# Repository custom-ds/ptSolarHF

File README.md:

# ptSolarHF
The ptSolar is the newest version of Project: Traveler's series of APRS trackers. The ptSolar has been designed and optimized for low-power operation, especially when using a solar panel.

Under the hood, the ptSolar runs on the same __Microchip ATMega328p__ microcontroller that the other trackers have been using for years, although this board runs at a lower 3.3 volt level, and a slower 8MHz clock speed.

A 2m VHF transmitter is provided by the __SA818S-V__ transmitter-on-a-chip system, which means it's frequency agile and can be used throughout the world.

The GPS receiver is utilizes the __ATGM336H__ GPS engine which has a light-weight footprint while being a cost-effective solution. The ATGM336H is capable of position reports in excess of 60,000', making it a suitable solution for high altitude (latex) balloons traveling to over 100,000'.

## The Circuit Board
The circuit board is designed in Kicad and features a 4-layer design with castellated solder points for the attached solar panels.

The ptSolar is currently in the prototyping stages. Version 1.1.0 of the PCB was the initial design that was first built in early 2025, and includes the ATMega328p microcontroller, an ATGM336H GPS receiver, and the SA818S-V VHF transmitter. VHF signal filtering is provided by a 3-pole pi filter, reducing spurious harmonic output to well within Part 97 specifications.

## The Breakout Board
A Breakout board has been developed that can be temporarily or permanently paired to the top of the ptSolar tracker. The breakout includes a second ISCP programming port, a second serial data interface for configuring the tracker, a Sparkfun Qwiic connector for interfacing with other I2C sensors.

There is also a 2.1mm barrel jack for accepting power from a battery pack, along with the required 5V regulator when operating at higher supplied voltages. 

The Breakout Board mates to the tracker with a female .1" header connecting into the 6-pin (ISCP) and 8-pin (Serial, I2C) plugs on the ptSolar.

## Preparing the IDE for the Firmware
In the Arduino IDE and go to File &rarr; Preferences.  In the Additional Boards Manager URLs field, add the URL to the Project: Traveler website .json file:

```
https://www.projecttraveler.org/downloads/package_projecttraveler_index.json
```

Note that if there's already something in that field, you can click the small icon to the right of the text field where you are allowed to enter multiple entries on multiple lines.

Click OK to close the preferences dialog.  Then go to Tools &rarr; Boards &rarr; Boards Manager.

When the Boards Manager opens, select "Contributed" from the Type drop-down.  In the resulting list, you should find the Project Traveler Boards by Project Traveler option.  Click the Install button in the lower-right corner.

Close out of the Boards Manager dialog, and the back under Tools &rarr; Board, you should see "ptSolar Tracker (Arduino as ISP)" near the bottom of the list. 

## Setting the Controller Flags
If this is a brand new ptSolar board that has never been programmed before, there are several commands that must be run from a DOS command prompt. If the ptSolar was purchased as an assembled and tested kit, you can skip these steps.

The fuses are to be set as follows:
* Low: 0xFF
* High: 0xD6
* Extended: 0xFD

To program the fuses using the AVRDude tool (which is included in the Arduino IDE, and works with the Arduino As ISP programmer), open a command prompt on the PC.

```
C:\> cd \Program Files (x86)\Arduino\hardware\tools\avr\bin
C:\...> avrdude.exe -p m328p -b 19200 -c avrisp -C ..\etc\avrdude.conf -P comX* -U lfuse:w:0xDF:m -U hfuse:w:0xD6:m -U efuse:w:0xFD:m
```
Depending on your installation of the Arduino IDE, your avrdude may also be found in:

```
C:\Users\{Username}\AppData\Local\Arduino15\packages\arduino\tools\avrdude\6.3.0-arduino17\bin
```

This will write the fuses to the new processor.  To verify that the fuses have been written, run these commands:

```
avrdude.exe -p m328p -b 19200 -c avrisp -C ..\etc\avrdude.conf -P comX* -U lfuse:w:0xFF:m -U hfuse:w:0xD6:m -U efuse:w:0xFD:m 
```

\* Replace "comX" with whatever Com port your ArduinoISP is enumerating on.

### Verifying the Fuses
```
C:\...> avrdude.exe -p m328p -b 19200 -c avrisp -C ..\etc\avrdude.conf -P comX* -U lfuse:r:lowfuse:h -U hfuse:r:highfuse:h -U efuse:r:exfuse:h
C:\...> type lowfuse
C:\...> type highfuse
C:\...> type exfuse
```

\* Replace "comX" with whatever Com port your ArduinoISP is enumerating on.

## Loading the Firmware
To program the ptSolar, open the firmware Sketch in this GitHub Repository in the Arduino IDE. 

Go to the Tools &rarr; Board menu, select the "ptSolar Tracker (Arduino as ISP)" from the list of targets.  

The ptSolar boards are automatically configured to use the Arduino as ISP programmer to load the firmware onto the tracker boards, so no further configuration is necessary. Click the Upload button which will cause the Sketch to compile and will program to the ATmega328 processor similarly to how a normal Arduino board is programmed.

Sometimes it is necessary to apply external power to the ptSolar Tracker, depending on how much current the Programmer board is capable of sourcing.

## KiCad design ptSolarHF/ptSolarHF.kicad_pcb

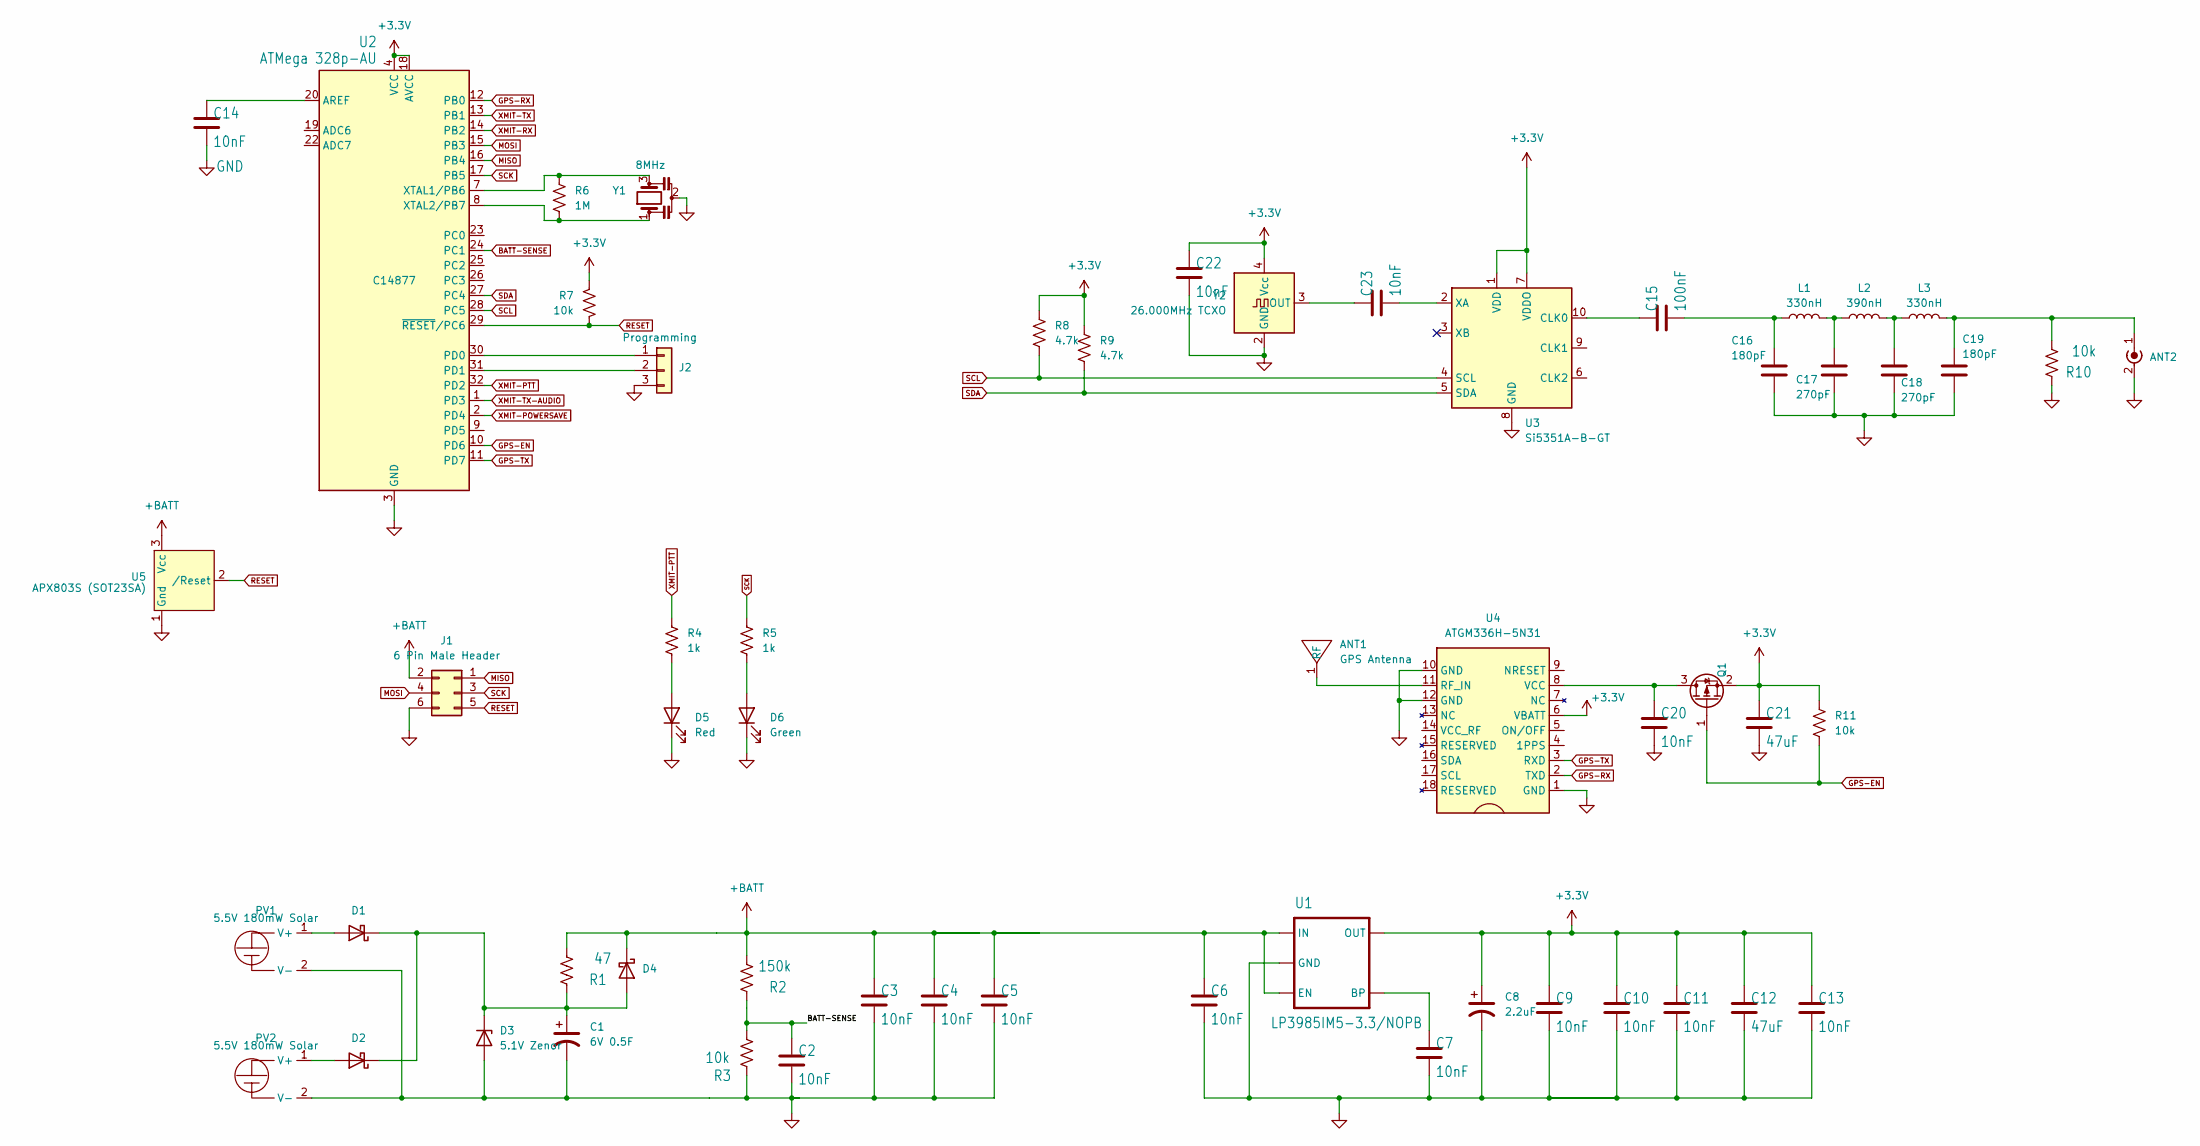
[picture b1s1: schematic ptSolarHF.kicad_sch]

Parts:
ANT1: GPS Antenna; Pulse ANT8010LL05R1575A Antenna; Digikey 553-ANT8010LL05R1575ACT-ND
ANT2: SMA Edge Mount (Optional); SMA_Samtec_SMA-J-P-H-ST-EM1_EdgeMount; Digikey CON-SMA-EDGE-S-ND
C1: 6V 0.5F; CDS CSP Super Cap 8mm dia; Digikey 4688-CSP-6R0L504R-TW-ND
C2, C3, C4, C5, C6, C7, C9, C10, C11, C13, C14, C20, C22, C23: 10nF; C_0805_2012Metric; Digikey 399-1158-1-ND
C8: 2.2uF; C_0805_2012Metric; Digikey 445-1420-1-ND
C12, C21: 47uF; C_0805_2012Metric; Digikey 399-C0805C476M9PACTUCT-ND
C15: 100nF; C_0805_2012Metric; Digikey 399-C0805C104K5RACTUCT-ND
C16, C19: 180pF; C_0805_2012Metric; Digikey 490-11541-1-ND
C17, C18: 270pF; C_0805_2012Metric; Digikey 490-9738-1-ND
D1, D2, D4: CDBA340L-G Schottky; D_SMA; Digikey 641-1258-1-ND
D3: 5.1V Zenor; D_SOD-123; Digikey MMSZ5231B-FDICT-ND
D5: Red; D_0805_2012Metric; Digikey LTST-C171KRKT
D6: Green; D_0805_2012Metric; Digikey LTST-C171GKT
J1: 6 Pin Male Header; PinHeader_2x03_P2.54mm_Vertical; Digikey 732-5394-ND
J2: Programming; PinHeader_1x03_P2.54mm_Vertical; Digikey 732-5316-ND
L1, L3: 330nH; L_0805_2012Metric; Digikey 490-5672-1-ND
L2: 390nH; L_0805_2012Metric; Digikey 490-5673-1-ND
PV1, PV2: 5.5V 180mW Solar; PowerFilm MPT3.6-75; Digikey 1996-1020-ND
Q1: DMP2004K-7; SOT-23; Digikey DMP2004KDICT-ND
R1: 47; R_2512_6332Metric; Digikey YAG3404CT-ND
R2: 150k; R_0805_2012Metric; Digikey 311-150KCRCT-ND
R3, R7, R10, R11: 10k; R_0805_2012Metric; Digikey 13-RT0805FRD0710KLCT-ND
R4, R5: 1k; R_0805_2012Metric; Digikey 311-1.0KARCT-ND
R6: 1M; R_0805_2012Metric; Digikey 311-1.0MARCT-ND
R8, R9: 4.7k; R_0805_2012Metric; Digikey 311-4.7KARCT-ND
U1: LP3985IM5-3.3/NOPB; SOT-23-5; Digikey LP3985IM5-3.3/NOPBCT-ND
U2: ATMega 328p-AU; TQFP-32_7x7mm_P0.8mm; Digikey ATMEGA328P-AU-ND
U3: Si5351A-B-GT; MSOP-10_3x3mm_P0.5mm; Digikey 336-2399-5-ND
U4: ATGM336H-5N31; Digikey ALIEXPRESS
U5: APX803S (SOT23SA); SOT-23; Digikey APX803S-31SA-7DICT-ND
Y1: 8MHz; Resonator_SMD_Murata_CSTxExxV-3Pin_3.0x1.1mm; Digikey 490-CSTNE8M00G520000R0CT-ND
Y2: 26.000MHz TCXO; Oscillator_SMD_SeikoEpson_TG2520SMN-xxx-xxxxxx-4Pin_2.5x2.0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; LCSC C3013793

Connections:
+3.3V: C8.1, C9.1, C10.1, C11.1, C12.1, C13.1, C21.1, C22.1, Q1.2 (S), R7.1, R8.1, R9.1, R11.1, U1.5 (OUT), U2.4 (VCC), U2.6 (VCC), U2.18 (AVCC), U3.1 (VDD), U3.7 (VDDO), U4.6 (VBATT), Y2.4 (Vcc)
+BATT: C3.1, C4.1, C5.1, C6.1, D4.1 (K), J1.2, R1.2, R2.2, U1.1 (IN), U1.3 (EN), U5.3 (Vcc)
BATT-SENSE: C2.1, R2.1, R3.2, U2.24 (PC1)
GND: ANT2.2 (Ext), C1.2, C2.2, C3.2, C4.2, C5.2, C6.2, C7.2, C8.2, C9.2, C10.2, C11.2, C12.2, C13.2, C14.2, C16.1, C17.1, C18.1, C19.1, C20.2, C21.2, C22.2, D3.2 (A), D5.1 (K), D6.1 (K), J1.6, J2.3, PV1.2 (V-), PV2.2 (V-), R3.1, R10.1, U1.2 (GND), U2.3 (GND), U2.5 (GND), U2.21 (GND), U3.8 (GND), U4.1 (GND), U4.10 (GND), U4.12 (GND), U5.1 (Gnd), Y1.2, Y2.2 (GND)
GPS-EN: Q1.1 (G), R11.2, U2.10 (PD6)
GPS-RX: U2.12 (PB0), U4.2 (TXD)
GPS-TX: U2.11 (PD7), U4.3 (RXD)
MISO: J1.1, U2.16 (PB4)
MOSI: J1.4, U2.15 (PB3)
unnamed: ANT1.1 (RF), U4.11 (RF_IN)
unnamed: ANT2.1 (In), C19.2, L3.2, R10.2
unnamed: C15.2, C16.2, L1.1
unnamed: C17.2, L1.2, L2.1
unnamed: C18.2, L2.2, L3.1
unnamed: D1.2 (A), PV1.1 (V+)
unnamed: C1.1, D1.1 (K), D2.1 (K), D3.1 (K), D4.2 (A), R1.1
unnamed: D2.2 (A), PV2.1 (V+)
unnamed: D5.2 (A), R4.2
unnamed: D6.2 (A), R5.2
unnamed: J2.1, U2.30 (PD0)
unnamed: J2.2, U2.31 (PD1)
unnamed: C20.1, Q1.3 (D), U4.8 (VCC)
unnamed: C7.1, U1.4 (BP)
unnamed: C14.1, U2.20 (AREF)
unnamed: R6.1, U2.7 (XTAL1/PB6), Y1.3
unnamed: R6.2, U2.8 (XTAL2/PB7), Y1.1
unnamed: C15.1, U3.10 (CLK0)
unnamed: C23.2, U3.2 (XA)
unnamed: C23.1, Y2.3 (OUT)
RESET: J1.5, R7.2, U2.29 (~RESET/PC6), U5.2 (/Reset)
SCK: J1.3, R5.1, U2.17 (PB5)
SCL: R8.2, U2.28 (PC5), U3.4 (SCL)
SDA: R9.2, U2.27 (PC4), U3.5 (SDA)
XMIT-POWERSAVE: U2.2 (PD4)
XMIT-PTT: R4.1, U2.32 (PD2)
XMIT-RX: U2.14 (PB2)
XMIT-TX: U2.13 (PB1)
XMIT-TX-AUDIO: U2.1 (PD3)

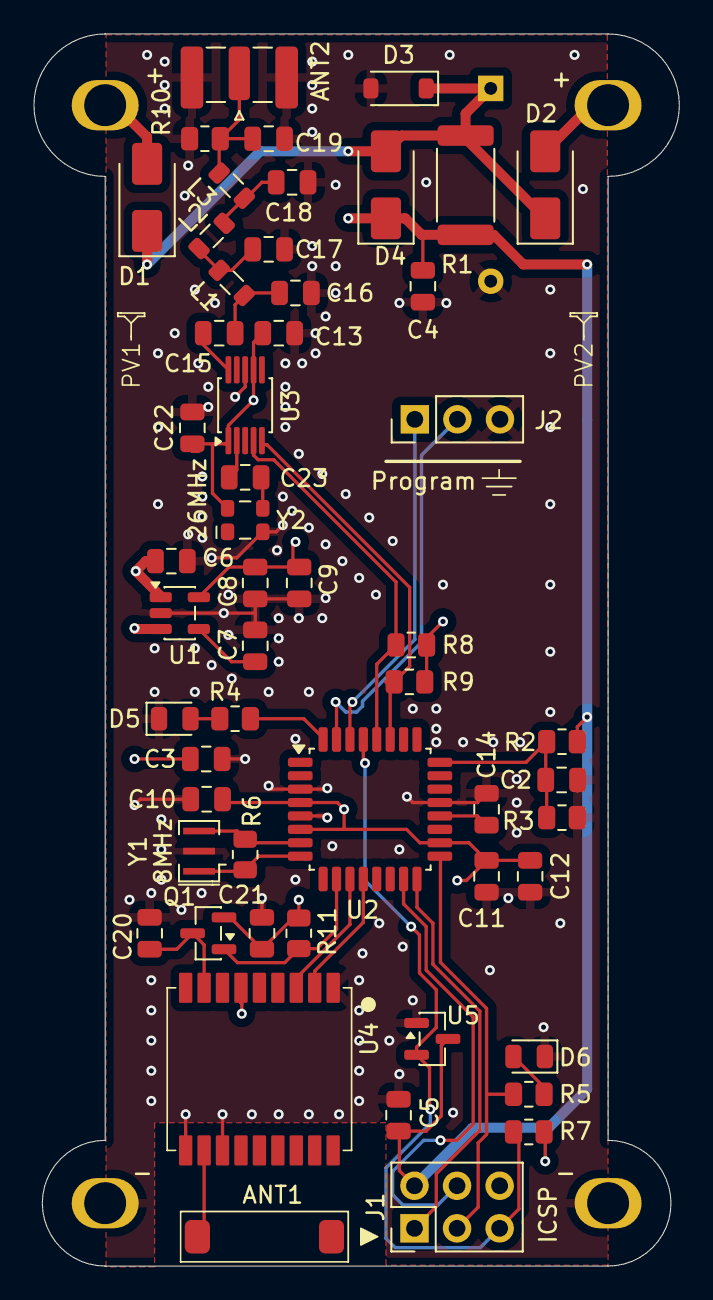
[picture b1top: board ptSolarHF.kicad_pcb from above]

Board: 4 copper layers, 38.5 x 73.5 mm, 57 parts (1 on the bottom side), 34 nets.

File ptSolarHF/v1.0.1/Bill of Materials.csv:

"Reference","Value","Datasheet","Footprint","Qty","DNP","Digikey","LCSC"
"ANT1","GPS Antenna","","Custom DS:Pulse ANT8010LL05R1575A Antenna","1","","553-ANT8010LL05R1575ACT-ND","C3284202"
"ANT2","SMA Edge Mount (Optional)","~","Connector_Coaxial:SMA_Samtec_SMA-J-P-H-ST-EM1_EdgeMount","1","","CON-SMA-EDGE-S-ND",""
"C1","6V 0.5F","~","Custom DS:CDS CSP Super Cap 8mm dia","1","","4688-CSP-6R0L504R-TW-ND",""
"C2,C3,C4,C5,C6,C7,C9,C10,C11,C13,C14,C20","10nF","~","Capacitor_SMD:C_0805_2012Metric","12","","399-1158-1-ND","C83170"
"C8","2.2uF","~","Capacitor_SMD:C_0805_2012Metric","1","","445-1420-1-ND","C107128"
"C12,C21","47uF","~","Capacitor_SMD:C_0805_2012Metric","2","","399-C0805C476M9PACTUCT-ND","C16780"
"C15","100nF","~","Capacitor_SMD:C_0805_2012Metric","1","","399-C0805C104K5RACTUCT-ND","C49678"
"C16,C19","180pF","~","Capacitor_SMD:C_0805_2012Metric","2","","490-11541-1-ND","C113826"
"C17,C18","270pF","~","Capacitor_SMD:C_0805_2012Metric","2","","490-9738-1-ND","C527183"
"D1,D2,D4","CDBA340L-G Schottky","~","Diode_SMD:D_SMA","3","","641-1258-1-ND","C22364900"
"D3","5.1V Zenor","~","Diode_SMD:D_SOD-123","1","","MMSZ5231B-FDICT-ND","C85181"
"D5","Red","~","Diode_SMD:D_0805_2012Metric","1","","LTST-C171KRKT","C2295"
"D6","Green","~","Diode_SMD:D_0805_2012Metric","1","","LTST-C171GKT","C2297 "
"J1","6 Pin Male Header","~","Connector_PinHeader_2.54mm:PinHeader_2x03_P2.54mm_Vertical","1","","732-5394-ND",""
"J2","Programming","~","Connector_PinHeader_2.54mm:PinHeader_1x03_P2.54mm_Vertical","1","","732-5316-ND",""
"L1,L3","330nH","~","Inductor_SMD:L_0805_2012Metric","2","","490-5672-1-ND","C184530"
"L2","390nH","~","Inductor_SMD:L_0805_2012Metric","1","","490-5673-1-ND","C108076"
"PV1,PV2","5.5V 180mW Solar","https://www.powerfilmsolar.com/hubfs/documents/spec%20sheets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","Custom DS:PowerFilm MPT3.6-75","2","","1996-1020-ND",""
"Q5","DMP2004K-7","","Package_TO_SOT_SMD:SOT-23","1","","DMP2004KDICT-ND","C332297"
"R1","47","~","Resistor_SMD:R_2512_6332Metric","1","","YAG3404CT-ND","C513678"
"R2","150k","~","Resistor_SMD:R_0805_2012Metric","1","","311-150KCRCT-ND","C114558"
"R3,R7,R10,R11","10k","~","Resistor_SMD:R_0805_2012Metric","4","","13-RT0805FRD0710KLCT-ND","C100047"
"R4,R5","1k","~","Resistor_SMD:R_0805_2012Metric","2","","311-1.0KARCT-ND","C95781"
"R6","1M","~","Resistor_SMD:R_0805_2012Metric","1","","311-1.0MARCT-ND","C107700"
"R8,R9","4.7k","~","Resistor_SMD:R_0805_2012Metric","2","","311-4.7KARCT-ND","C60816"
"U1","LP3985IM5-3.3/NOPB","https://www.ti.com/lit/ds/symlink/lp3985.pdf?HQS=dis-dk-null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","Package_TO_SOT_SMD:SOT-23-5","1","","LP3985IM5-3.3/NOPBCT-ND","C108877"
"U2","ATMega 328p-AU","https://ww1.microchip.com/downloads/en/DeviceDoc/Atmel-7810-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","Package_QFP:TQFP-32_7x7mm_P0.8mm","1","","ATMEGA328P-AU-ND","C14877"
"U3","Si5351A-B-GT","https://www.silabs.com/documents/public/data-sheets/Si5351-B.pdf","Package_SO:MSOP-10_3x3mm_P0.5mm","1","","336-2399-5-ND","C504891"
"U4","ATGM336H-5N31","https://www.tinytronics.nl/product_files/002176_ATGM336H.pdf","Custom DS:ATGM336H-5N31","1","","ALIEXPRESS","C90770"
"U5","APX803S (SOT23SA)","","Package_TO_SOT_SMD:SOT-23","1","","APX803S-31SA-7DICT-ND","C129757"
"Y1","8MHz","~","Crystal:Resonator_SMD_Murata_CSTxExxV-3Pin_3.0x1.1mm","1","","490-CSTNE8M00G520000R0CT-ND","C907975"
"Y2","27MHz Xtal - 7M-27.000MEEQ-T","~","Crystal:Crystal_SMD_3225-4Pin_3.2x2.5mm","1","","887-1328-1-ND","C2450429"

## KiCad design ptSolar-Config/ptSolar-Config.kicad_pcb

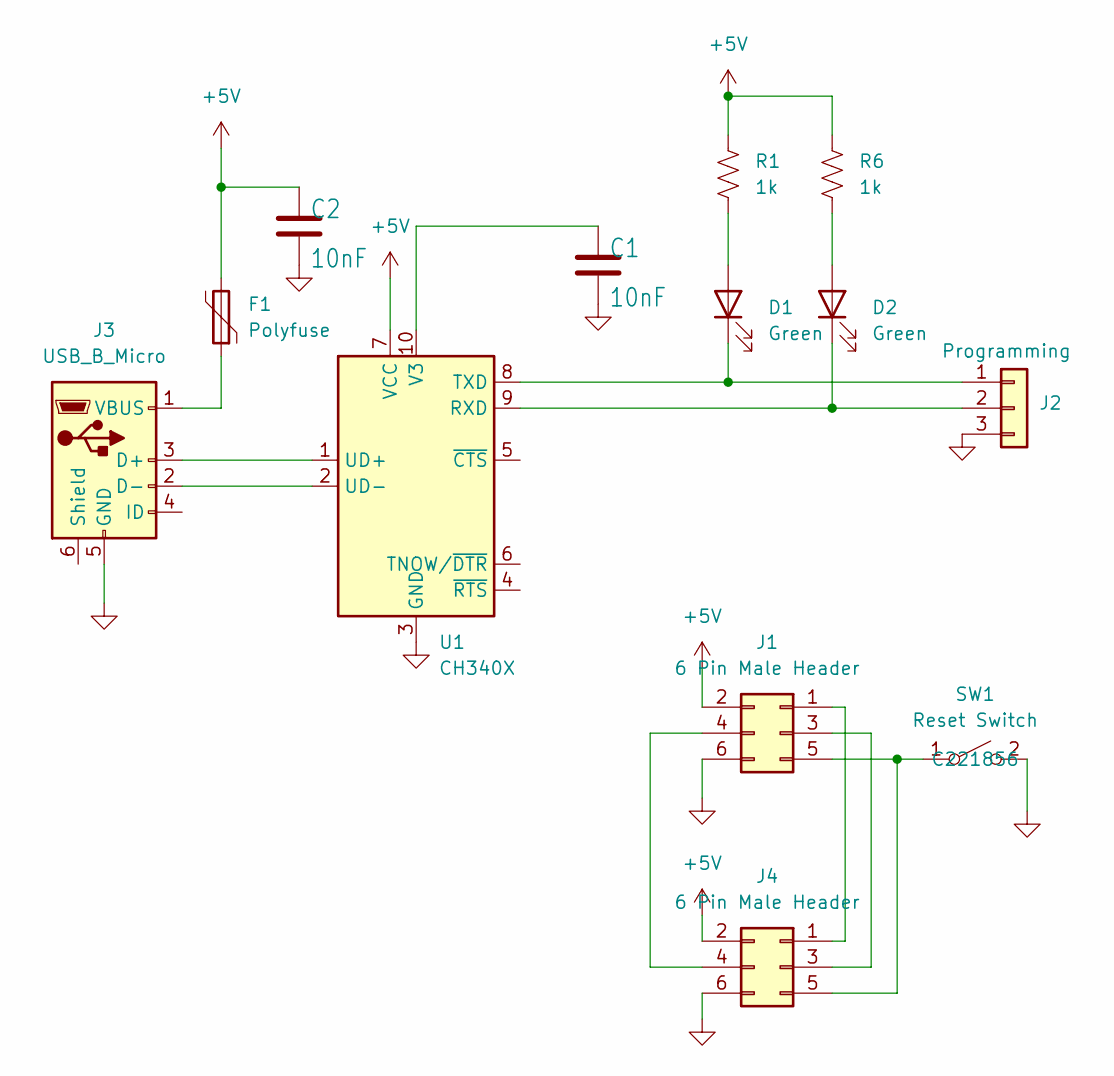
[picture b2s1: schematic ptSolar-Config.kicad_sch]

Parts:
C1, C2: 10nF; C_0805_2012Metric; Digikey 399-1158-1-ND
D1, D2: Green; D_0805_2012Metric; Digikey LTST-C171GKT
F1: Polyfuse; Fuse_1206_3216Metric; Digikey 507-1794-1-ND
J1, J4: 6 Pin Male Header; PinHeader_2x03_P2.54mm_Vertical; Digikey 732-5394-ND
J2: Programming; PinHeader_1x03_P2.54mm_Vertical; Digikey 732-5316-ND
J3: USB_B_Micro; USB_Micro-B_Wuerth_629105150521; LCSC C2894326
R1, R6: 1k; R_0805_2012Metric; Digikey 311-1.0KARCT-ND
SW1: Reset Switch; SW_SPST_PTS647_Sx38; Digikey CKN9104CT-ND
U1: CH340X; MSOP-10_3x3mm_P0.5mm; LCSC CH340X

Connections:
+5V: C2.1, F1.2, J1.2, J4.2, R1.1, R6.1, U1.7 (VCC)
GND: C1.2, C2.2, J1.6, J2.3, J3.5 (GND), J4.6, SW1.2 (B), U1.3 (GND)
unnamed: D1.2 (A), R1.2
unnamed: D1.1 (K), J2.1, U1.8 (TXD)
unnamed: D2.2 (A), R6.2
unnamed: D2.1 (K), J2.2, U1.9 (RXD)
unnamed: J1.1, J4.1
unnamed: J1.3, J4.3
unnamed: J1.4, J4.4
unnamed: J1.5, J4.5, SW1.1 (A)
unnamed: J3.3 (D+), U1.1 (UD+)
unnamed: J3.2 (D-), U1.2 (UD-)
unnamed: F1.1, J3.1 (VBUS)
unnamed: C1.1, U1.10 (V3)

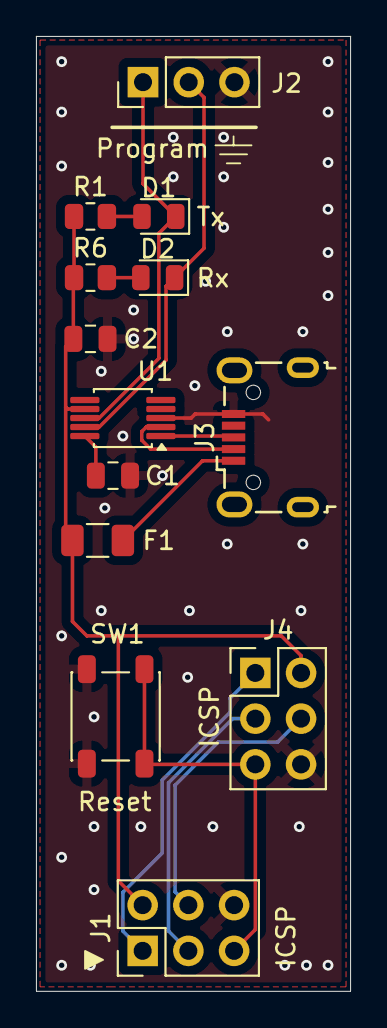
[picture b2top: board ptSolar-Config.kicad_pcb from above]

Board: 2 copper layers, 17.4 x 53.0 mm, 13 parts (0 on the bottom side), 14 nets.

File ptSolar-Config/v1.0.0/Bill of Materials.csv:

"Reference","Value","Datasheet","Footprint","Qty","DNP","Digikey","LCSC","LSCC"
"C1,C2","10nF","~","Capacitor_SMD:C_0805_2012Metric","2","","399-1158-1-ND","C83170",""
"D1,D2","Green","~","Diode_SMD:D_0805_2012Metric","2","","LTST-C171GKT","C2297 ",""
"F1","Polyfuse","~","Fuse:Fuse_1206_3216Metric","1","","507-1794-1-ND","C194142",""
"J1","6 Pin Male Header","~","Connector_PinHeader_2.54mm:PinHeader_2x03_P2.54mm_Vertical","1","","732-5394-ND","",""
"J2","Programming","~","Connector_PinHeader_2.54mm:PinHeader_1x03_P2.54mm_Vertical","1","","732-5316-ND","",""
"J3","USB_B_Micro","~","Connector_USB:USB_Micro-B_Wuerth_629105150521","1","","","C2894326",""
"R1,R6","1k","~","Resistor_SMD:R_0805_2012Metric","2","","311-1.0KARCT-ND","C95781",""
"SW1","Reset Switch","~","Button_Switch_SMD:SW_SPST_PTS647_Sx38","1","","CKN9104CT-ND","C221856",""
"U1","CH340X","https://cdn.sparkfun.com/assets/5/0/a/8/5/CH340DS1.PDF","Package_SO:MSOP-10_3x3mm_P0.5mm","1","","","CH340X",""

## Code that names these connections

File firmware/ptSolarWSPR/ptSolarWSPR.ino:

/*  WSPR_Si5351_wspr_enc_demo.ino
    Minimal WSPR beacon for ATmega328 (Uno/Nano) + Si5351 using:
      - Etherkit Si5351 library to generate the RF tones
      - wspr_enc.c (with nhash.c) to encode a WSPR message into 162 channel symbols

    References:
      - Etherkit Si5351 example shows centi-Hz use and WSPR spacing = 146 cHz. [ref]
      - WSPR protocol timing: 162 symbols, 1.4648 Hz spacing, 8192/12000 s per symbol. [ref]
*/


#define FIRMWARE_VERSION "1.6.0"
#define CONFIG_PROMPT "\n\n# "
#include "BoardDef.h"   //defines if this is a ptFlex, ptSolar, or ptSolarHF PCB board


#include <avr/wdt.h>

#include <si5351.h>
#include "wspr_enc.h"
#include "nhash.h"

#include <int.h>
#include <string.h>

#include "GPS.h"


#include "Wire.h"





// -------- USER CONFIG --------
static char    CALL[] = "W0ZC";
static char    GRID[] = "EM18";
static uint8_t PWR_dBm = 23;

//static const uint32_t WSPR_BASE_FREQ_HZ = 14097200UL;   // 14.095.600 + 1600Hz
static const uint32_t WSPR_BASE_FREQ_HZ = 21096200UL;   // 21.094.600 + 1600Hz
//static const uint32_t WSPR_BASE_FREQ_HZ = 28126200UL;   // 28.124.600 + 1600Hz
static const int32_t  SI5351_CORRECTION_PPB = 0;        // e.g. -1200 = -1.2 ppm
static const si5351_drive SI5351_CLK0_DRIVE = SI5351_DRIVE_8MA;
// ------ END USER CONFIG ------

static const uint16_t WSPR_TONE_SPACING_CENTI_HZ = 146; // ≈1.46 Hz
static const uint16_t WSPR_SYMBOL_COUNT           = 162;
static const uint16_t WSPR_TONE_MS                = 683; // 8192/12000 s


//PD0 is Serial Port RX
//PD1 is Serial Port TX
#define PIN_PTT_OUT 2     //PD2
//PD3 is not used
//PD4 is not used
#define PIN_AUDIO 5       //PD5   - Audio Annunciation
#define PIN_GPS_EN 6      //PD6
#define PIN_GPS_TX 7      //PD7

#define PIN_GPS_RX 8      //PB0
//PB1 is not used
//PB2 is not used
//PB3 is MOSI
//PB4 is MISO
#define PIN_LED 13        //PB5

//Analog Pins
//PC0 is not used
#define PIN_ANALOG_BATTERY A1   //PC1
//PC2 is not used
//PC3 is not used
//PC4 is SDA
//PC5 is SCL
//PC6 is reset and not available

Si5351 si5351;
static uint8_t wspr_symbols[WSPR_SYMBOL_COUNT];
GPS GPSParser(PIN_GPS_RX, PIN_GPS_TX, PIN_GPS_EN);                                      //Object that parses the GPS strings


static void build_wspr_symbols() {
    char pwr_str[4];
    itoa(PWR_dBm, pwr_str, 10);
    uint8_t mtype = wspr_enc(CALL, GRID, pwr_str, wspr_symbols); // fills 162 symbols

    // quick blink = message type
    for (uint8_t i = 0; i < mtype; i++)
    {
        wdt_reset();
        digitalWrite(PIN_PTT_OUT, HIGH);
        delay(80);
        digitalWrite(PIN_PTT_OUT, LOW);
        delay(80);
    }
}

static void transmit_wspr_once() {
    const uint64_t base_cHz = (uint64_t)WSPR_BASE_FREQ_HZ * 100ULL;

    // Serial.println("Starting WSPR transmission...");
    delay(100);
    si5351.output_enable(SI5351_CLK0, 1);
    digitalWrite(PIN_PTT_OUT, HIGH);

    for (uint16_t i = 0; i < WSPR_SYMBOL_COUNT; i++)
    {
        wdt_reset();
        // Serial.print("Transmitting symbol ");;
        // Serial.println(i);
        
        const uint8_t sym = wspr_symbols[i] & 0x03;
        const uint64_t f_cHz = base_cHz + (uint64_t)sym * (uint64_t)WSPR_TONE_SPACING_CENTI_HZ;
        si5351.set_freq(f_cHz, SI5351_CLK0);
        delay(WSPR_TONE_MS);
    }

    si5351.output_enable(SI5351_CLK0, 0);
    digitalWrite(PIN_PTT_OUT, LOW);
    Serial.println("WSPR transmission complete.");
    //delay(100);
}

void setup() {
    wdt_disable(); // disable the watchdog timer by default
    wdt_enable(WDTO_8S);    //Enable the Watchdog if configured
    wdt_reset();

    Serial.begin(19200);
    Serial.println("WSPR Si5351 Transmitter Demo");

    pinMode(PIN_PTT_OUT, OUTPUT);
    digitalWrite(PIN_PTT_OUT, HIGH);
    delay(1000);
    wdt_reset();

    // Starting the wire
    Serial.println("Wire begin");
    delay(100);
    Wire.begin();


    Serial.println("set bus speed");
    delay(100);
    Wire.setClock(100000); // Set to 400kHz

    byte error, address;
    int nDevices = 0;
/*
    Serial.println("Scanning I2C bus...");
    delay(100);
    for (address = 1; address < 127; address++)
    {
        wdt_reset();
        Serial.print("Checking address 0x");
        Serial.println(address, HEX);
        delay(100);
        Wire.beginTransmission(address);
        error = Wire.endTransmission();

        if (error == 0)
        {
            Serial.print(F("I2C device found at address 0x"));
            delay(100);
            if (address < 16)
                Serial.print('0');
            Serial.print(address, HEX);
            Serial.println(F("  !"));
            delay(100);
            nDevices++;
        }
        else if (error == 4)
        {
            Serial.print(F("Unknown error at address 0x"));
            delay(100);
            if (address < 16)
                Serial.print('0');
            Serial.println(address, HEX);
            delay(100);
        }
    }

    if (nDevices == 0)
        Serial.println(F("No I2C devices found\n"));
    else
        Serial.println(F("done\n"));

    delay(1000);
*/
    Serial.println(F("Initializing Si5351..."));
    delay(100);
    wdt_reset();
    si5351.init(SI5351_CRYSTAL_LOAD_10PF, 27000000, 0);

    Serial.println("Correction");
    delay(100);
    wdt_reset();
    si5351.set_correction(SI5351_CORRECTION_PPB, SI5351_PLL_INPUT_XO);

    Serial.println("Drive");
    delay(100);
    si5351.drive_strength(SI5351_CLK0, SI5351_CLK0_DRIVE);

    Serial.println("Output");
    delay(100);
    si5351.output_enable(SI5351_CLK0, 0);

    Serial.println("Done");
    delay(1000);

    Serial.println(F("Building WSPR symbols..."));
    delay(1000);
    build_wspr_symbols();
    Serial.println(F("Got them"));
    delay(1000);
    // Optional: wait for even minute before calling transmit_wspr_once()
    Serial.println("Press p to transmit WSPR once");

    GPSParser.setDebugNEMA(true); /// TODO: Need to pull this from Configuration
    GPSParser.setDebugLevel(2);   // Get full verbose output from the GPS
}

void loop() {
    byte byTemp;
    wdt_reset();
    
    if (Serial.available())
    {
        byTemp = Serial.read();
        if (byTemp == 'p')
        {
            Serial.println("Transmitting");
            transmit_wspr_once(); // one full WSPR frame (~110.6 s)

            Serial.println("Press p to transmit WSPR once");
        }
    }
    delay(1000);
}

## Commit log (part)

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2026-01-25 Testing wspr_enc.c
2026-01-25 Back to a semi-working ptSolarHF. Still rebooting on 5351.
2026-01-25 ptSolarHF functions as a tester now.
2026-01-26 Tweaks to proof of concept. Updates to Schematics.
2026-01-26 ptSolarHF nearly at MVP.
2026-01-27 3D prints for carrier and neck attachment.
2026-01-27 Minor changes to 3D prints
2026-01-29 Approaching RC
2026-01-31 Refining type 1 vs type 2-3 operation. Configuration data finalized.
2026-02-01 Enabled multi-packet type 2-3 transmissions.
2026-02-02 Minor tweaks to arrive at 1.0
2026-02-03 Version 1.0.0 RC, along with python script to push to APRS-IS
2026-02-05 1.0 RC2 to fix issues with the GPS loosing lock between Type 2 and 3 packets.
2026-02-05 Updates to python converter.
2026-02-06 Updated converter script to support multiple balloons, and maintain persistence between restarts. Prototype new rib design for mounting supports.
2026-02-15 Firmware 1.0 RC3. Updates to the 3d carriers,
2026-02-15 Converter.py fix for when wsprnet doesn't return any results.
2026-02-25 Implementing fine altitude modulation.
2026-02-28 Finalizing PCB v1.0.1
2026-03-01 Added Configuration board to project
2026-03-12 Tweaks to converter.
2026-04-21 Updated to firmware 1.0.1
2026-04-26 Moved configuration cable into separate ptConfig project.
2026-04-29 Tweaks to convert.py to track total flight time.
2026-05-31 Limiting GPS debug noise. Updates to converter to include position logging and KML file creation.
2026-06-10 Fix for Converter.py logging, and updateding to firmware 1.0.2 to not disable the GPS during transmission.
2026-06-21 Fix to multi-band enumeration comments.
2026-06-29 Reverting changes from 1.0.2 to disable GPS during xmit.
2026-06-29 Reverting changes to converter.py
